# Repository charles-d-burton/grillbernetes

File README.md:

# Grillbernetes

A collection of software and infrastructure to manage a Smoker or other temperature managed device with Kubernetes.  Keep in mind that this was designed to work on a K8S cluster that was local to the network.  I would appreciate some help getting SSL in order on STAN to that it could be connected to any K8S cluster.  Keep in mind that some knowledge of K8S is necessary to get this to work.

### Requirements
* Go 1.12+
* Kubernetes 1.14+
* A working Kubernetes Cluster with the following:
  * Certmanager
  * A forwarded Service and Ingress
* Raspberry Pi(s) or other SBC
* DS18B20 Sensors
* Relays
* Some device that needs relatively precise temperature control
* (Other things that I've likely forgotten)

### Building the components(Other than the PiSmoker)
Run:
```bash
$./build.sh -u <your dockerhub username>
```

This will build and upload the artifacts to your personal Docker Hub compiled for
* ARM
* ARM64
* AMD64

Projects are configured to pull in the correct image based on your SBC arch.

## Components By Directory
Review the README for each piece for technical details.
### Cluster Setup
Collection of Kubernetes/Terraform Files that setup the base layer necessary.  It will install the NATS and NATS Streaming operators, services, and deployments to coalesce a fully functioning NATS Streaming Cluster.  Optionally there is code in there to setup Traefik as an Ingress to your cluster.  Read the README in that directory for more information.

### Control Hub
The program and K8S installation files to build/deploy the control mechanism.  This allows you to take control of a device and turn it on/off as well as set the desired temperature state.

### Events
Consumes the event stream from NATS Streaming and publishes it to the `/events/` path using Server Side Events.  Is literally just an event stream, more to come for multi-device control.

### Frontend
WIP

### PiSmoker
Program to interface and control a Smoker attached to a Raspberry Pi.

### Vue-Frontend
SPA(WIP)

### Global TODO:
* Align topic handling to be configurable in all services
* Allow event publisher to serve multiple topics
* Set control hub to allow control of multiple topics
* (Maybe those should be kubeless?)

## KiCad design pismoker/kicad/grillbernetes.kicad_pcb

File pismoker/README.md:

# PiSmoker

Interfaces with a Raspberry Pi and a DS18b20 sensor to send updates to a data stream as well as provide a mechanism to control the temperatures settings.  It uses the PID algorithm to ensure the temperature stays level.  Any correctly wired DS18b20 Sensor will work with this software.  The fastest time resolution you can get is about 1 second.

### Requirements
* Go 1.12+
* Raspberry Pi
* DS18b20 (I used the MAX31850k from Adafruit)
* Relay (I used a BEM 40a SSR)
* A NATS Streaming Host to publish data to

### Building

```bash
$go get -u
$go build -o pismoker
```

### Installation
Ensure you modify the `pismoker.service` file to point to your NATS Streaming host.
```bash
$cp pismoker $HOME/
$sudo cp scrips/pismoker.service /etc/systemd/system/
$sudo systemctl daemon-reload && systemctl enable pismoker && systemctl start pismoker
```

### TODO
* Handle multiple temperature sensors and take an average
* Handle multiple relays (not sure on this one)
* Integrate other sensor types such as smoke density and humidity
* Message bus abstraction to support other message bus types
* A learning mode to figure out the Kp, Ki, Kd optimizations

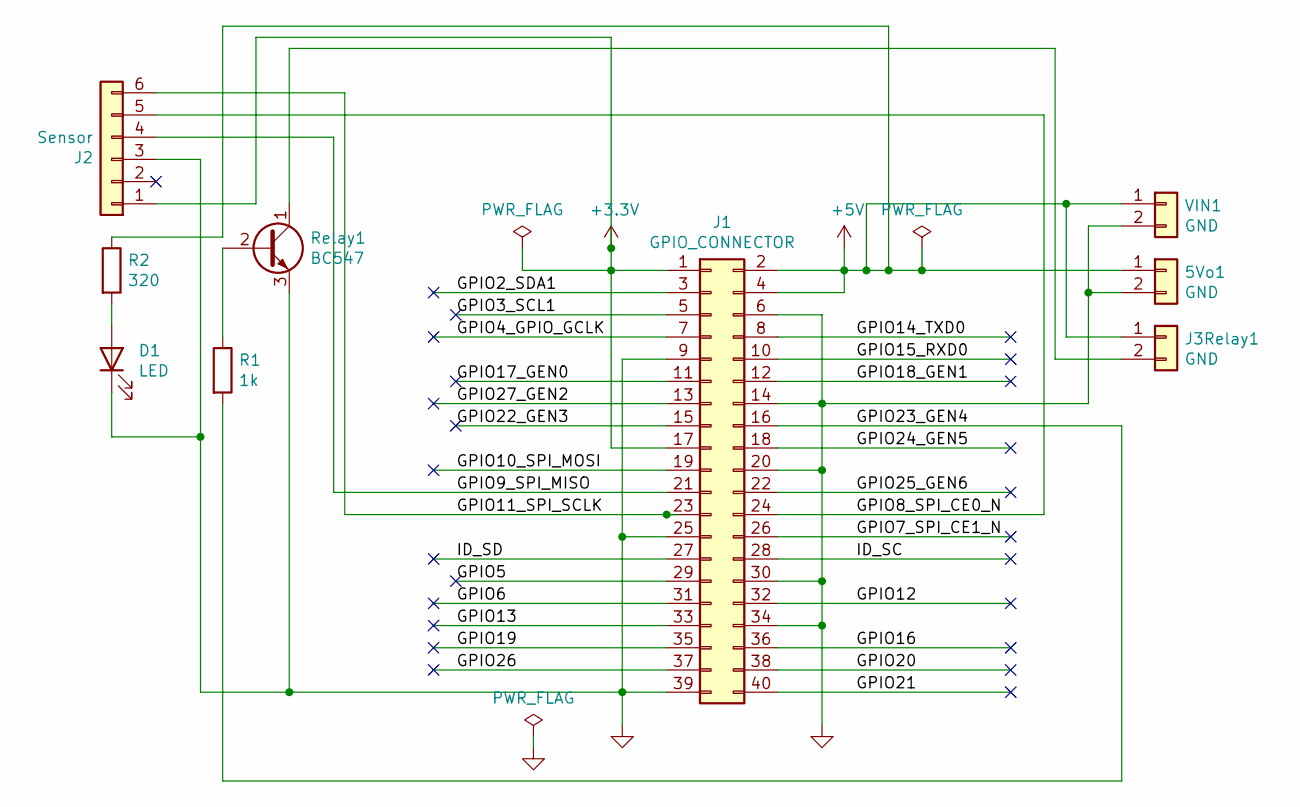
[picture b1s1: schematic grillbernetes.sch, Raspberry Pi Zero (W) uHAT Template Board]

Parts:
5Vo1: GND; JST_EH_B2B-EH-A_1x02_P2.50mm_Vertical
D1: LED; LED_D5.0mm
J1: GPIO_CONNECTOR; PinSocket_2x20_P2.54mm_Vertical_Centered_Anchor
J2: Sensor; PinHeader_1x06_P2.54mm_Vertical
J3Relay1: GND; JST_EH_B2B-EH-A_1x02_P2.50mm_Vertical
R1: 1k; R_Axial_DIN0207_L6.3mm_D2.5mm_P7.62mm_Horizontal
R2: 320; R_Axial_DIN0207_L6.3mm_D2.5mm_P7.62mm_Horizontal
Relay1: BC547; TO-92
VIN1: GND; JST_EH_B2B-EH-A_1x02_P2.50mm_Vertical

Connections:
+3V3: J1.1, J1.17, J2.1
+5V: 5Vo1.1, J1.2, J1.4, J3Relay1.1, R2.1, VIN1.1
/GPIO2_SDA1: J1.3
/GPIO3_SCL1: J1.5
/GPIO4_GPIO_GCLK: J1.7
/GPIO5: J1.29
/GPIO6: J1.31
/GPIO7_SPI_CE1_N: J1.26
/GPIO8_SPI_CE0_N: J1.24, J2.5
/GPIO9_SPI_MISO: J1.21, J2.4
/GPIO10_SPI_MOSI: J1.19
/GPIO11_SPI_SCLK: J1.23, J2.6
/GPIO12: J1.32
/GPIO13: J1.33
/GPIO14_TXD0: J1.8
/GPIO15_RXD0: J1.10
/GPIO16: J1.36
/GPIO17_GEN0: J1.11
/GPIO18_GEN1: J1.12
/GPIO19: J1.35
/GPIO20: J1.38
/GPIO21: J1.40
/GPIO22_GEN3: J1.15
/GPIO23_GEN4: J1.16, R1.2
/GPIO24_GEN5: J1.18
/GPIO25_GEN6: J1.22
/GPIO26: J1.37
/GPIO27_GEN2: J1.13
/ID_SC: J1.28
/ID_SD: J1.27
GND: 5Vo1.2, D1.1 (K), J1.6, J1.9, J1.14, J1.20, J1.25, J1.30, J1.34, J1.39, J2.3, Relay1.3 (E), VIN1.2
unnamed: D1.2 (A), R2.2
unnamed: J3Relay1.2, Relay1.1 (C)
unnamed: R1.1, Relay1.2 (B)

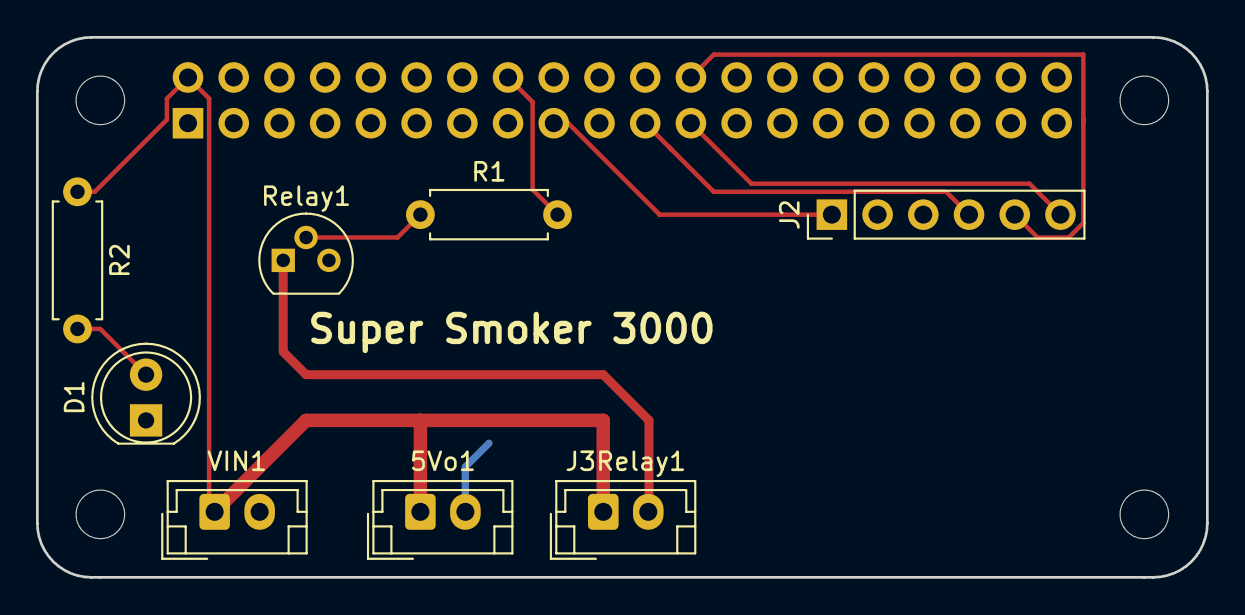
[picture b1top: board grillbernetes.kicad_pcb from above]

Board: 2 copper layers, 65.0 x 30.0 mm, 13 parts (1 on the bottom side), 10 nets.

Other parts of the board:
H1, H2, H3, H4: MountingHole; MountingHole_2.7mm_M2.5_uHAT_RPi

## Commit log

2019-06-22 feat: initial work
2019-06-22 feat: build system
2019-06-23 feat: better buildenv
2019-06-27 feat: added control-hub
2019-06-27 feat: start monorepo
2019-06-27 fixes
2019-06-27 build system fixes
2019-06-29 feat: added control hub
2019-06-29 feat: build system works
2019-07-06 feat: added vuetify frontend
2019-07-07 feat: frontend work
2019-07-07 crud: logging events
2019-07-07 fix: output full stream data
2019-07-07 stuff
2019-07-07 crud: added stub for mock
2019-07-20 feat: lots of things
2019-07-20 fix: comments
2019-07-20 feat: starting terraform work
2019-07-20 terraform work
2019-07-20 feat: added smoker
2019-07-20 feat: Readmes
2019-07-21 crud: cleanups
2019-07-25 feat: added fibonacci backoff to control hub
2019-07-28 feat: started work for connection pooling
2019-07-28 fix: channels
2019-08-03 feat: backoff/retry on smoker code
2019-08-03 fix: better handling
2019-08-03 feat: control hub retry
2019-08-03 feat: updating to logrus
2019-08-03 fix: non-blocking smoker
2019-08-03 crud: better logging
2019-08-03 fix: receiver init
2019-08-03 fix: more logging
2019-08-03 fix: removed reset
2019-08-03 fix: controlstate init
2019-08-18 feat: added flutter
2019-08-24 feat: manifest workflow
2019-08-24 fix: manifest
2019-08-24 feat: push images
2019-08-24 fix: push images
2019-08-24 fix: run
2019-08-24 fix: reverting
2019-08-24 use script
2019-08-24 more manifest updates
2019-09-06 fix: build
2019-09-06 feat: parallel builds
2019-09-06 fix: permissions
2019-09-06 fix: buidl
2019-09-06 fix: variable scope
2019-09-07 feat: starting work on better connection handling
2019-09-07 fix: debugging
2019-09-07 fix: build output
2019-09-09 feat: simplifying publisher code
2019-09-12 fix: version updates
2019-09-12 fix: updates
2019-09-22 feat: implement traefik
2019-09-22 fix: added traefik deployment
2019-09-30 feat: traefik implemented
2019-10-06 feat: converted controlhub to redis
2019-10-13 feat: major refactor
2019-10-13 feat: start run loop in smoker
2019-10-13 fix: added SSL back in
2019-10-13 fix: comma in bash array
2019-10-13 fix: control hub deployment args
2019-10-14 fix: handle key not found
2019-10-14 fix: make build fail sooner
2019-10-14 fix: progress of build
2019-10-17 feat: added device lookup
2019-10-17 fix: build script
2019-10-17 fix: buildscript
2019-10-18 feat: implemented device auto registration/cleanup
2019-10-18 build(deps): bump eslint-utils from 1.3.1 to 1.4.2 in /vue-frontend
    Bumps [eslint-utils](https://github.com/mysticatea/eslint-utils) from 1.3.1 to 1.4.2.
    - [Release notes](https://github.com/mysticatea/eslint-utils/releases)
    - [Commits](https://github.com/mysticatea/eslint-utils/compare/v1.3.1...v1.4.2)
2019-10-18 build(deps): bump lodash.defaultsdeep in /vue-frontend
    Bumps [lodash.defaultsdeep](https://github.com/lodash/lodash) from 4.6.0 to 4.6.1.
    - [Release notes](https://github.com/lodash/lodash/releases)
    - [Commits](https://github.com/lodash/lodash/compare/4.6.0...4.6.1)
2019-10-18 build(deps): bump lodash from 4.17.11 to 4.17.15 in /vue-frontend
    Bumps [lodash](https://github.com/lodash/lodash) from 4.17.11 to 4.17.15.
    - [Release notes](https://github.com/lodash/lodash/releases)
    - [Commits](https://github.com/lodash/lodash/compare/4.17.11...4.17.15)
2019-10-18 fix: redis connection in pubhub
2019-10-18 fix: aligned all paths
2019-10-21 fix: smoker code fixes, connection id fixes
2019-10-21 fix: bind POST function
2019-10-24 feat: large refactor of pismoker device
2019-11-08 feat: base functionality
2020-04-21 feat: add vugu wasm app
2020-04-24 crud: fix for cors
2020-04-24 fix: update to go 1.14
2020-04-24 fix: cors
2020-04-24 fix: wasm rendering now works
2020-04-24 feat: removed vue
2020-05-15 unknown
2020-05-15 fix: gomod
2020-05-24 feat: added new sensor type
2020-05-24 fix: nil pointer from sp close
2020-05-24 fix: put reading in channel
2020-05-24 fix: make relay controllable from pin
2020-05-25 fix: memory leak around sensor initialization
2020-05-27 feat: large update with better error handling
2020-05-27 fix: add subscriber error detection
2020-05-27 fix: null pointer
2020-05-27 fix: removed unncessary cleanup
2020-05-29 feat: switched to normal ingress
2020-05-30 fix: updated ingresses
2020-05-30 fix: updated pod counts
2020-06-01 feat: created auth service
2020-06-01 feat: enable build
2020-06-01 feat: added gateway
2020-06-02 crud: update deploy
2020-06-02 feat: added liveness to pub-hub
2020-06-03 fix: liveness probe
2020-06-14 feat: upgrading build
2020-06-14 fix: build errors
2020-06-14 feat: more build pipes
2020-06-14 fix: log healthz
2020-06-14 fix: pub-hub deployment file
2020-06-14 feat: healthchecks everywhere
2020-06-14 crud: removed old build file
2020-06-28 adding debugging
2020-06-28 feat: convert login to json
2020-06-29 feat: initial graphql work
2020-06-29 feat: convert auth to json
2020-07-03 feat: jsoniter everywhere
2020-07-05 feat: mvp grapql user service
2020-07-05 feat: breakup workflows
2020-07-05 feat: breakup builds
2020-07-05 fix: yaml syntax
2020-07-05 fix: yaml consistency
2020-07-05 feat: build gateway
2020-07-06 fix: move functions out of resolver file
2020-07-06 feat: rebuild on specific changes
2020-07-06 fix: better error handling
2020-07-06 use raw byte array
    Looks like jsoniter.rawmessage doesn't work as expected.
2020-07-06 Update Dockerfile
2020-08-01 feat: updated schema
2020-08-02 feat: hkeys redis, byte arrays for performance
2020-08-02 fix: typos
2020-08-02 fix: jsoniter rawmessage handling
2020-08-02 fix: remove jsoniter, non-conformant rawmessage handling
2020-08-02 fix: data types
2020-08-02 fix: covert array to string before sending
2020-08-02 fix: raw message handling
2020-08-02 fix: remove jsoniter from control hub
2020-08-02 feat: get device list by group
2020-08-02 feat: use serial as id
2020-08-02 fix: typo
2020-08-02 fix: better device output
2020-08-31 fix: add username to otp
2020-09-02 fix: added debug symbol
2020-09-03 fix: debugging auth
2020-09-03 fix: headers
2020-09-27 feat: adding wasm app
2020-09-27 feat: more login flow logic
2020-09-27 feat: added auth manager
2020-09-27 feat: wasm breakout
2020-09-27 fix: separate logic by type
2020-09-27 feat: signup page
2020-09-27 feat: signup flow
2020-10-23 feat: added websockets
2020-10-23 fix: enable wss
2020-11-11 feat: started adding fleet core
2021-01-16 feat: adding argo
2021-01-16 fix: added environment parsing
2021-01-16 feat: update go mod
2021-01-16 feat: more argo
2021-01-16 Set Kustomization Docker Tag
2021-01-16 fix: consolidate build
2021-01-16 fix: consolidate builds
2021-01-16 fix: update deployments
2021-01-16 fix: namespacing
2021-01-18 fix: auth service
2021-01-26 feat: kicad for supersmoker
2021-01-31 feat: added gatt configuration to device
2021-01-31 fix: removed unnecessary variable assign
2021-03-07 fix: updated dependencies
2021-03-07 feat: started reworking flutter app
2021-03-07 crud: library updates
2021-03-27 chore: update ingress objects
2021-06-20 feat: added stream-manager for jetstream
2021-06-20 fix: more build for stream-manager
2021-06-20 fix: updated resources
2021-06-20 fix: kustomize
2021-06-20 fix: logging
2021-06-20 noop
2021-06-20 fix: stream manager yaml
2021-06-20 fix: stream manager
2021-07-09 fix: nats
2021-07-09 fea: updated pubhub to use jetstream
2021-07-09 chore: remove stream-manager
2021-07-09 feat: convert other services to jetstream
2021-07-11 fix: create stream
2021-07-11 fix: error handling
2021-07-11 fix: more stream updates
2021-07-11 fix: match more tokens
2021-07-19 fix: set content-type
2021-07-19 fix: cores
2021-07-19 fix: set header in right location
2021-10-23 chore: added debug message
2021-10-23 chore(deps): bump github.com/gin-gonic/gin in /control-hub
    Bumps [github.com/gin-gonic/gin](https://github.com/gin-gonic/gin) from 1.6.3 to 1.7.0.
    - [Release notes](https://github.com/gin-gonic/gin/releases)
    - [Changelog](https://github.com/gin-gonic/gin/blob/master/CHANGELOG.md)
    - [Commits](https://github.com/gin-gonic/gin/compare/v1.6.3...v1.7.0)
    ---
    updated-dependencies:

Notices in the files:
pismoker/kicad/grillbernetes.kicad_pcb:
This PCB design is licensed under MIT Open Source License.
pismoker/kicad/grillbernetes.sch:
This Schematic is licensed under MIT Open Source License.
